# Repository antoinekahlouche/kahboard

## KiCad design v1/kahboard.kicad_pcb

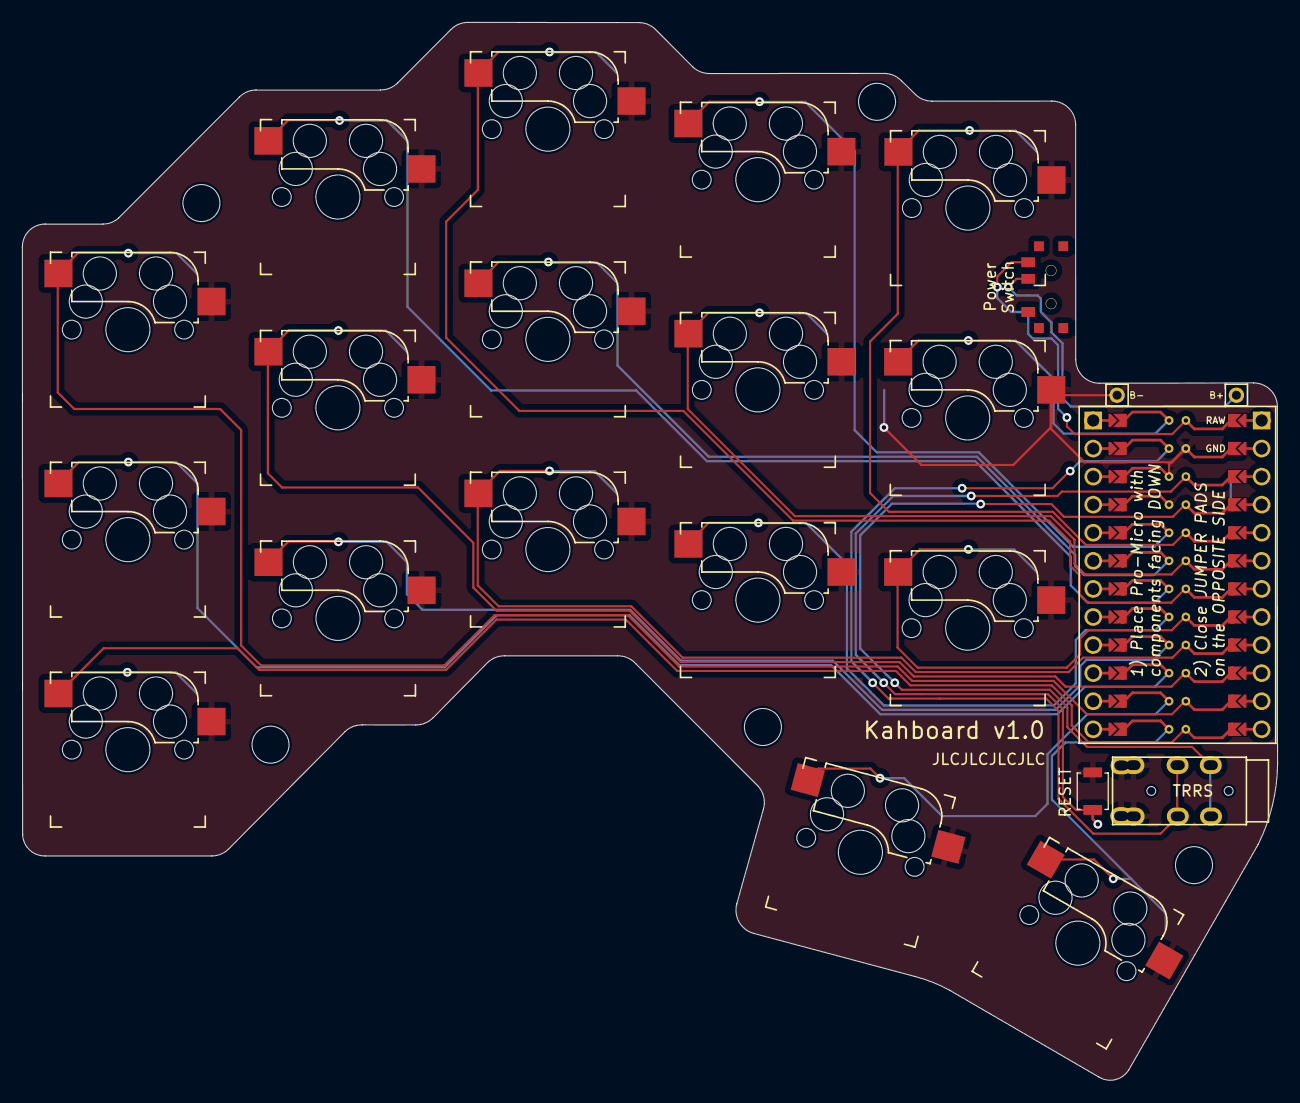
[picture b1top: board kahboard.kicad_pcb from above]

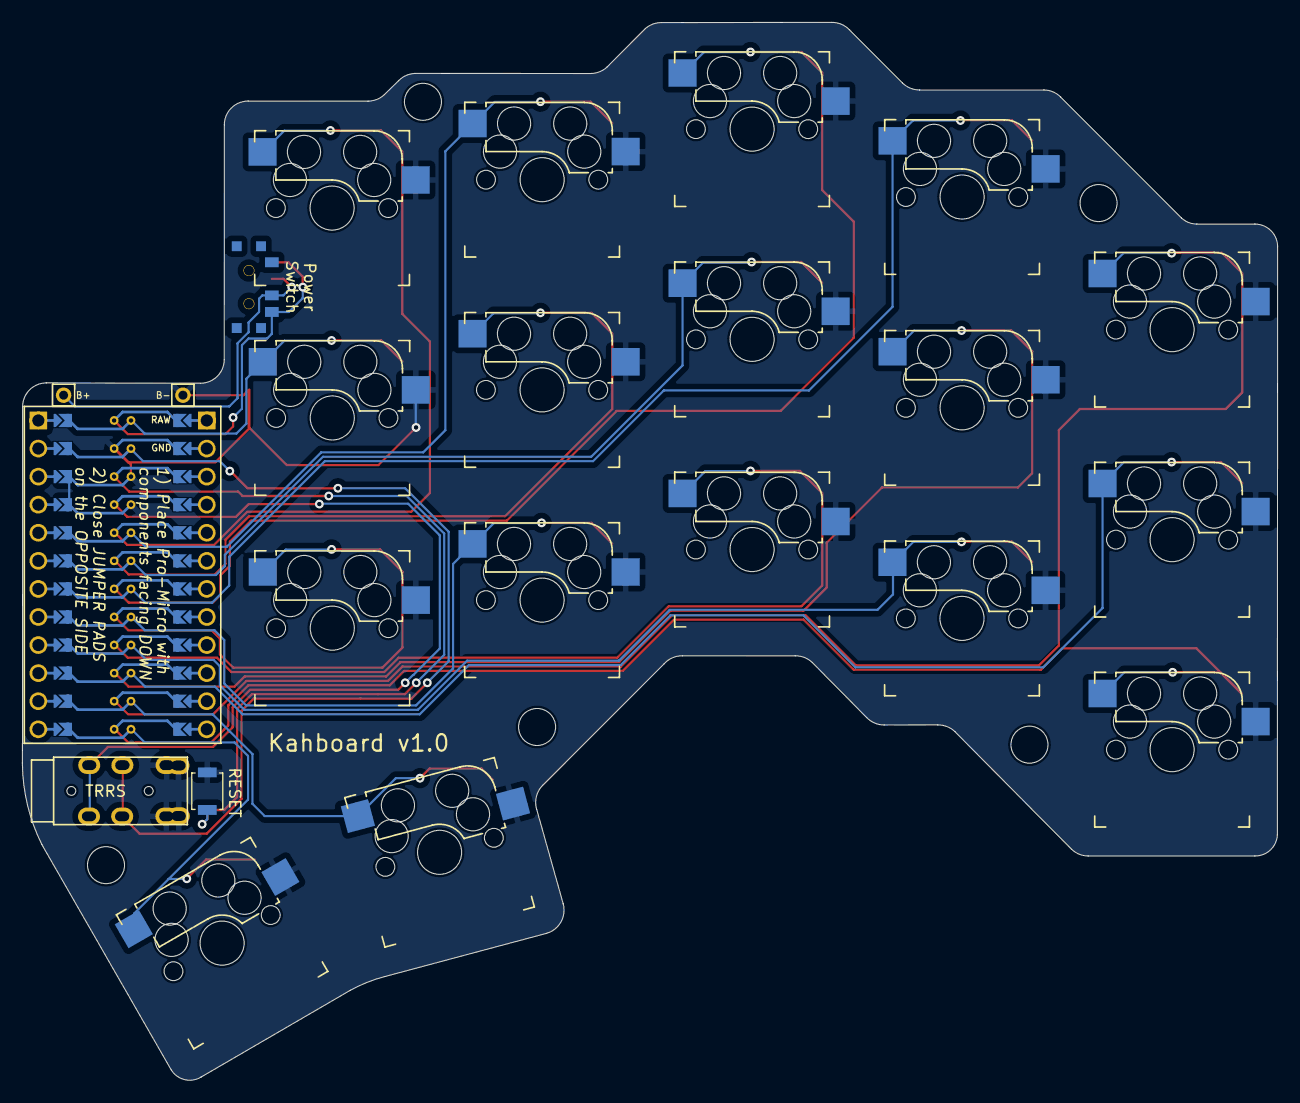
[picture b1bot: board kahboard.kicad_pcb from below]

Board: 2 copper layers, 113.6 x 95.7 mm, 30 parts (2 on the bottom side), 23 nets.

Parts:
Bat+r1: MountingHole_Pad; 1pin_conn
BatGND1: MountingHole_Pad; 1pin_conn
J2: AudioJack4dpb; TRRS-PJ-DPB2
Mounting 01, Mounting 02, Mounting 03, Mounting 04, Mounting 05: MountingHole_3.35mm
RST_B: SW_Push; SW_SPST_B3U-1000P
RST_F: SW_Push; SW_SPST_B3U-1000P
SW2, SW3, SW4, SW5, SW6, SW8, SW9, SW10, SW11, SW12, SW14, SW15, SW16, SW17, SW18, SW20, SW21: SW_Push; Kailh_socket_MX_reversible_sameside
SW_POWERR1: SW_SPDT; SPDT_C128955
SW_POWERR_BK: SW_SPDT; SPDT_C128955r
U1: ProMicro-kbd; ProMicro_facedown

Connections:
BT+_r: Bat+r1.1, SW_POWERR1.2, SW_POWERR_BK.2
Switch1: SW2.1, U1.10
Switch2: SW3.1, U1.17
Switch3: SW4.1, U1.18
Switch4: SW5.1, U1.19
Switch5: SW6.1, U1.20
Switch6: SW8.1, U1.16
Switch7: SW9.1, U1.15
Switch8: SW10.1, U1.14
Switch9: SW11.1, U1.13
Switch10: SW12.1, U1.1
Switch11: SW14.1, U1.5
Switch12: SW15.1, U1.6
Switch13: SW16.1, U1.7
Switch14: SW17.1, U1.8
Switch15: SW18.1, U1.9
Switch16: SW21.1, U1.11
Switch17: SW20.1, U1.12
Switch18: J2.R1, U1.2
gnd: BatGND1.1, J2.S, J2.T, RST_B.1, RST_F.1, SW2.2, SW3.2, SW4.2, SW5.2, SW6.2, SW8.2, SW9.2, SW10.2, SW11.2, SW12.2, SW14.2, SW15.2, SW16.2, SW17.2, SW18.2, SW20.2, SW21.2, U1.3, U1.4, U1.23
raw: SW_POWERR1.3, SW_POWERR_BK.3, U1.24
reset: RST_B.2, RST_F.2, U1.22
vcc: J2.R2, U1.21

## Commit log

2023-06-18 Missing drill file
2023-07-01 Arborescence
2023-07-01 Firmware
2023-07-01 Finlized keymap
2023-07-03 Working keyboard
2023-07-03 Invert layers nav and num
2023-07-03 Photo
2023-07-03 Rename README to README.md
2023-07-03 Invert backspace and space
2023-07-07 Upate design
2023-07-08 Case design
2023-07-08 Working firmware for mac and win
2023-07-09 Layout images
2023-07-09 Images
2023-07-09 To markdown
2023-07-10 Fix layout images
2023-07-14 Alt tab behavior and Colemak kc
2023-07-25 layout mac on left and win on right
2023-07-26 fix combo between split
2023-07-26 fix alt tab on windows
2023-07-28 standard numbers not keypad
2023-08-10 Simplify conf
2023-08-11 Update nav layer
2023-08-12 finished first design
2023-08-12 build script
2023-09-16 Moving volume buttons
2023-11-07 home and end keybinding on mac
2023-12-01 antislash and prtscr
2024-03-31 update layout to output azerty on windows & accents in one keystroke
2024-03-31 add macros
2024-04-04 no variables
2024-04-04 os detection
2024-04-04 fix overrides
2024-04-05 fix bitmask
2024-04-13 win spotlight
2024-05-11 Toggle os
2024-06-08 thumbnail
2024-07-07 invert numpad
2024-07-07 remove mac and win specific
2024-07-22 reverse numberpad
2024-09-26 fingerprints
2026-01-09 Update layout
2026-01-19 Refactor keyboard layout in layout.yml
2026-01-19 Update print statement from 'Hello' to 'Goodbye'
2026-01-19 Refactor keyboard layout in layout_totem.yml
2026-01-19 Fix key labels in layout_totem.svg
    Updated key labels in layout_totem.svg to reflect correct symbols.
